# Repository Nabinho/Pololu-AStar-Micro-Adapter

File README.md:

# Pololu-AStar-Micro-Adapter
Adapter PCB to Pololu AStar Micro Board.

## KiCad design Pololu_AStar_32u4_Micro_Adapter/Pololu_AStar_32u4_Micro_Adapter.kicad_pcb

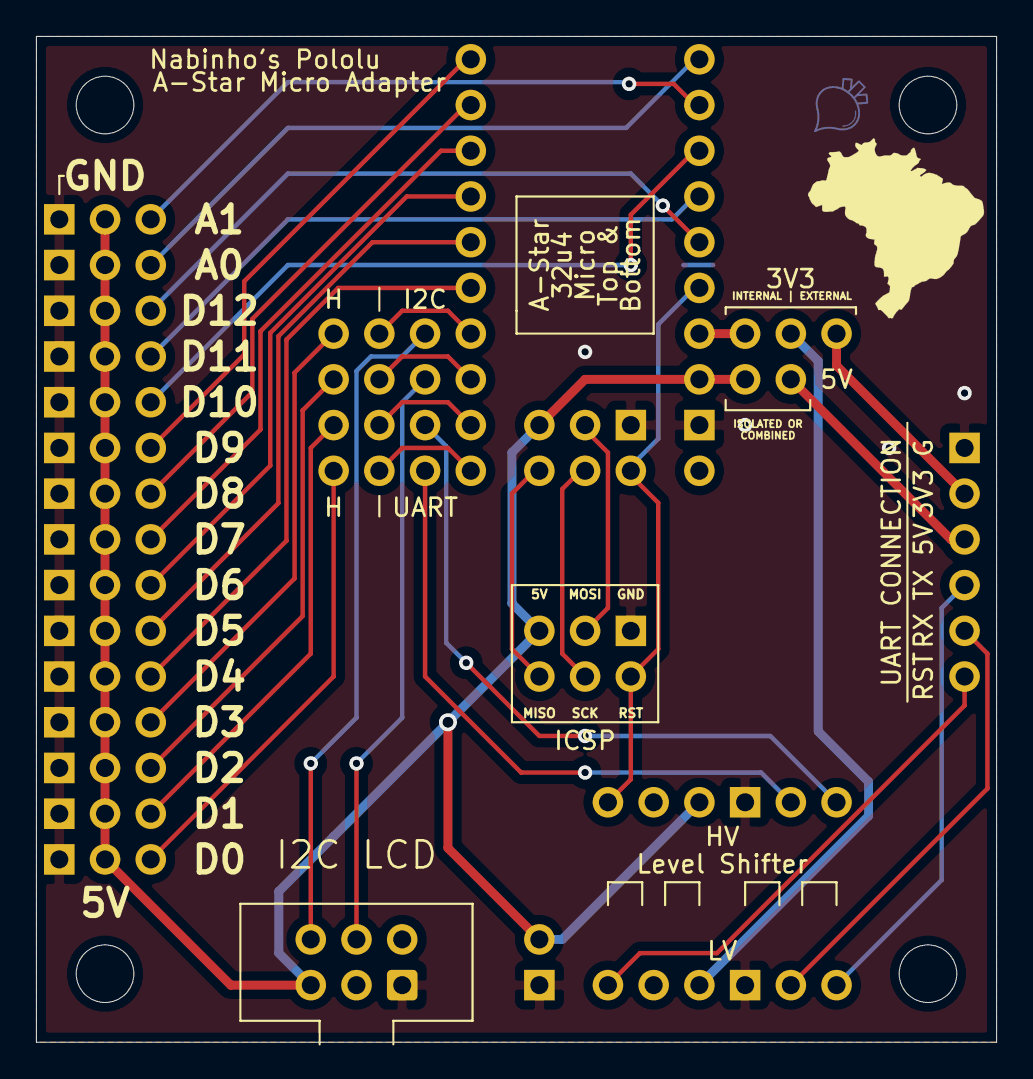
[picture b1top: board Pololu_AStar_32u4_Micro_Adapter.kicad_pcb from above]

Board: 2 copper layers, 53.3 x 55.9 mm, 13 parts (0 on the bottom side), 36 nets.

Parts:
C1: 1uF; PinHeader_1x02_P2.54mm_Vertical
J3, J4, J5, J6, J8: Conn_01x03; PinHeader_1x03_P2.54mm_Vertical_2
J7: Conn_02x03_Odd_Even; IDC-Header_2x03_P2.54mm_Vertical
J9: Conn_01x06; PinHeader_1x06_P2.54mm_Vertical
J10: Conn_01x02; PinHeader_1x02_P2.54mm_Vertical_2
J11: Conn_02x03_Odd_Even; PinHeader_2x03_P2.54mm_Vertical
J12: Conn_03x15; Digital_Header_Teensy_3.2_Adapter
J13: Conn_02x06_Odd_Even; Level_Shifter_RC
U1: PololuAStar_32u4Micro; PololuAStar_Micro

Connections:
0: J6.2, U1.10
0_H: J6.1, J12.1
1: J5.2, U1.9
1_H: J5.1, J12.2
2: J4.2, U1.8
2_H: J4.1, J12.3
3: J3.2, U1.7
3_H: J3.1, J12.4
4: J12.5, U1.6
5: J12.6, U1.5
6: J12.7, U1.4
7: J12.8, U1.3
8: J12.9, U1.2
9: J12.10, U1.1
10: J12.11, U1.13
11: J12.12, U1.14
12: J12.13, U1.15
+3V3: J8.3, U1.17
+5V: C1.1, J7.1, J10.2, J11.2, J12.16, J13.6, U1.18, U1.25
A0: J12.14, U1.11
A1: J12.15, U1.12
GND: C1.2, J7.5, J9.1, J11.6, J12.17, J13.7, J13.8, U1.19, U1.21
LV: J8.2, J13.5
MISO: J11.1, U1.26
MOSI: J11.4, U1.23
RST: J11.5, J13.2, U1.16, U1.22
RST_OUT: J9.6, J13.1
RX: J6.3, J13.10
RX_OUT: J9.5, J13.9
SCK: J11.3, U1.24
SCL: J3.3, J7.2
SDA: J4.3, J7.4
TX: J5.3, J13.12
TX_OUT: J9.4, J13.11
VCC: J9.3, J10.1
VCC_3V3: J8.1, J9.2
